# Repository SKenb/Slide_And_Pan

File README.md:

# Slide and Pan

## Overview 

    To give a timelapse that special touch, movement is essential. With this simple self-made and inexpensive slider, one can easily achieve that.

"Slide and Pan" stands for a small, compact, and "all in one" DIY slider.

### All in one

_Just place the Slider and start shooting._

The solution provides one small, solid metal box. (55 x 50 x 145 mm - TODO kg). So all required electronics and mechanics in it and no further motors, batteries, control devices are needed.

### Cheap

_Adjust the expenses to your budget._

One key argument for building an own Slider is the relatively small expenses compared to conventional Sliders. One might also think of requesting prepared or finished parts within a fair price ...

### DIY

_You are the boss_

The plans are no secret and easily be replicated by yourself. Just have a look at the public construction plans or come up with your own modified version.

### App

_Easy control_

Use the built-in rotary encoder or the App, to control the Slider. The App makes it very comfortable to set up movements and plan your shots.

## FEATURES

### Slide

Add linear movement to your Timelapse with the Slide-Feature.
Thereby, the Slider moves along a normed Alu-Profile, and thus any length you can think of is possible...

### Pan

Add some gorgeous rotation to your Timelapse
Keep the Milky Way in the center of the frame or focus another lovely spot during your shooting with the feature of (infinity) rotation of your camera ...

### TRACK

Use the Slider as Star-Tracker and realize detailed DeepSky exposures....

### Control

Select one of the predefined shots with the rotary-encoder or set up a detailed exposure/Timelapse with the inbuilt App...

### Compact

One of the most important factors is to have a small, compact and all in one gadget which fits in every backpack...

### Standalone

Everything included and thus no additional material is needed...

### Powerful

2 x 1500 mAh
Two powerful LiPo-batteries provide Slider with enough energy for several hours of shooting....

### Versatile

Nearly every position and movement one might think of is possible ...

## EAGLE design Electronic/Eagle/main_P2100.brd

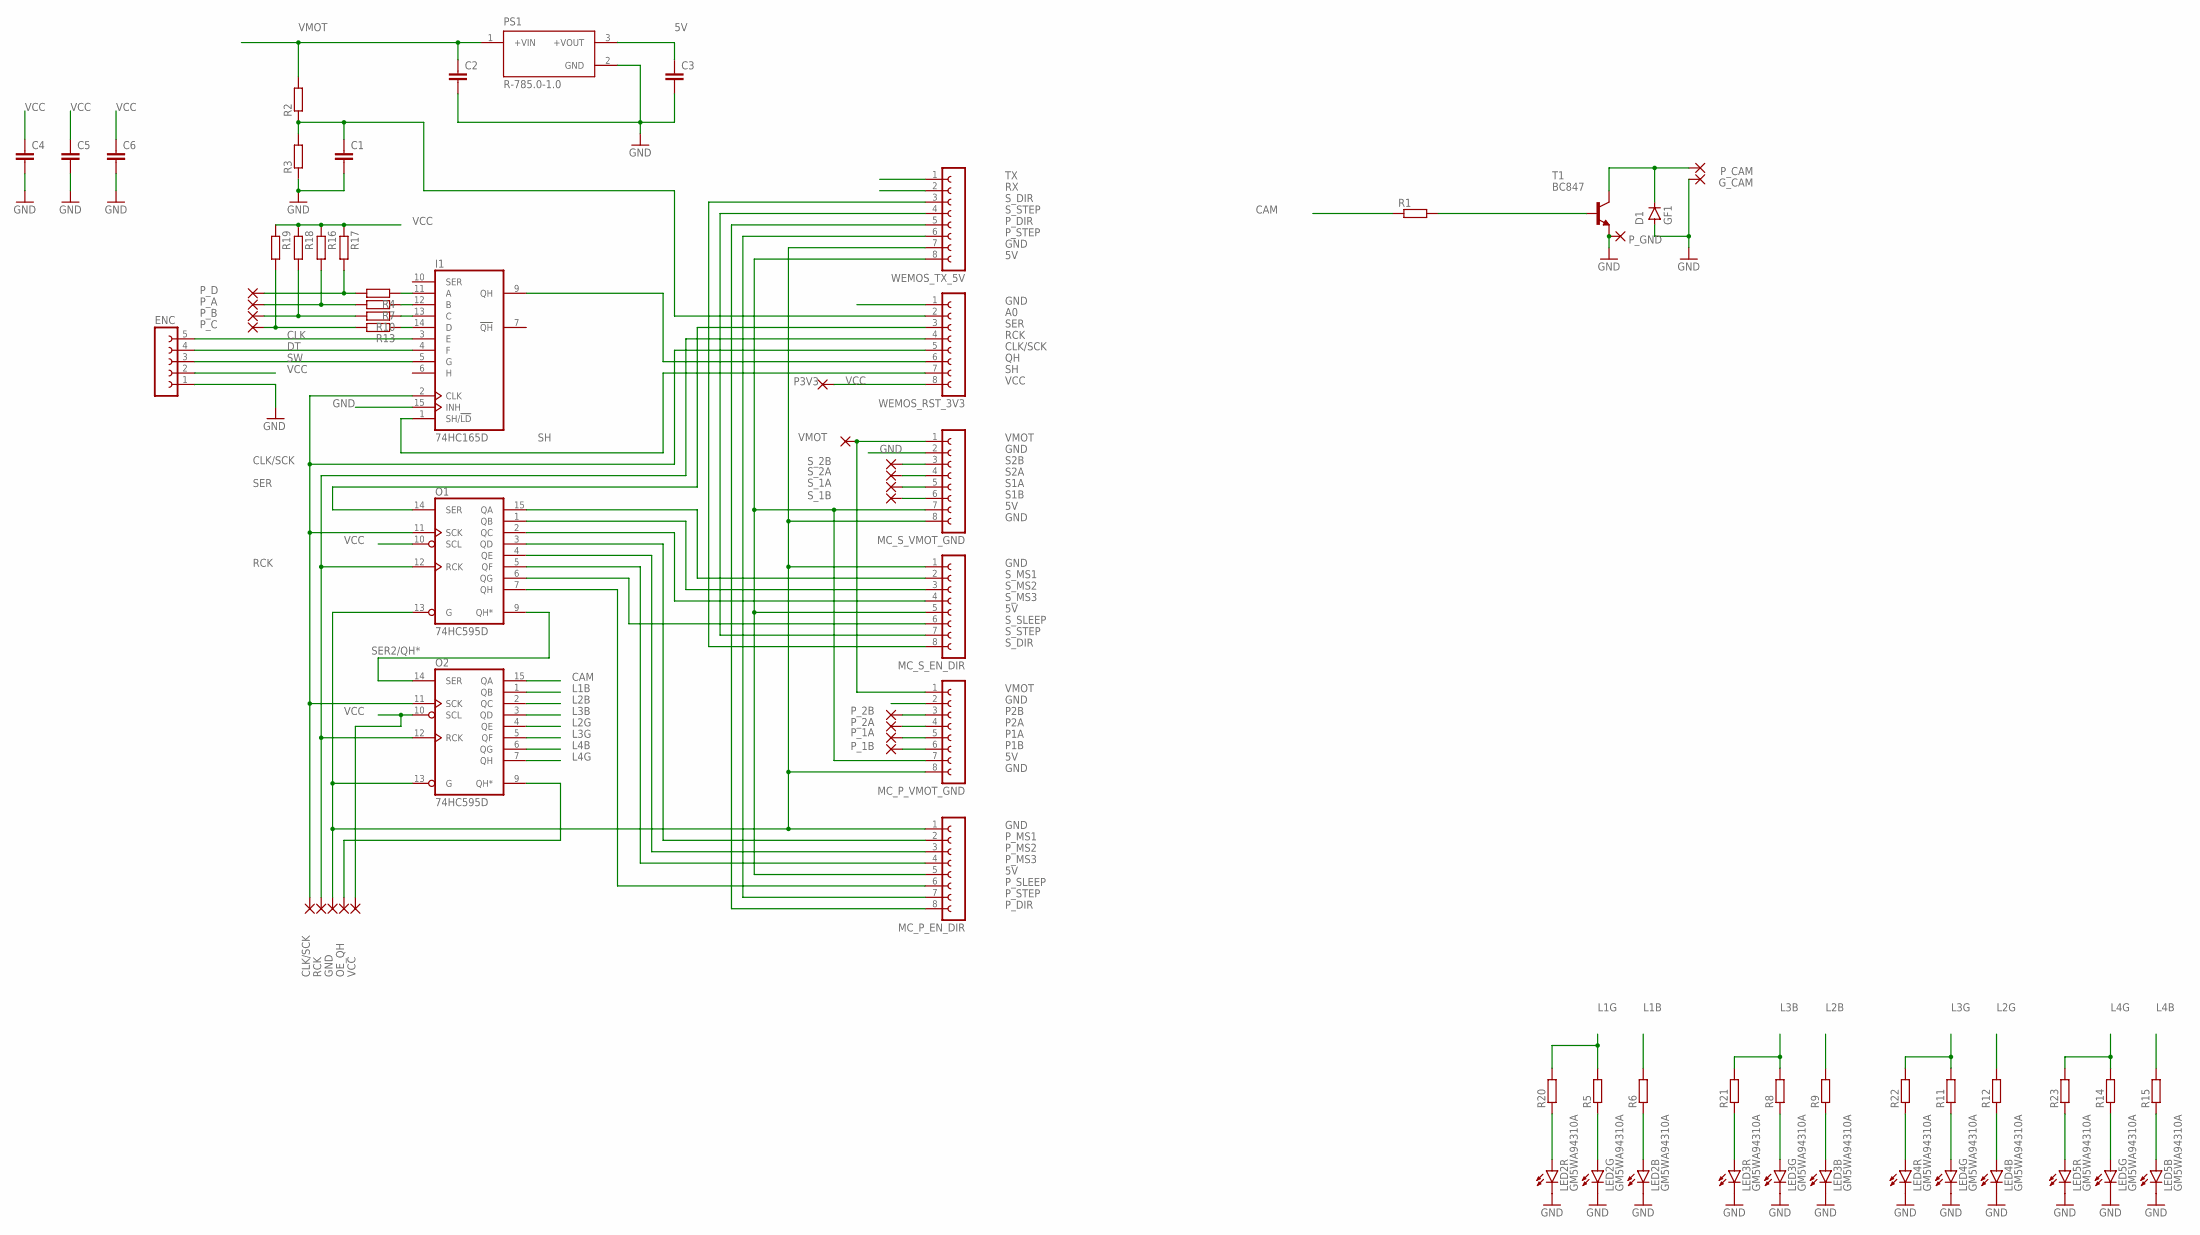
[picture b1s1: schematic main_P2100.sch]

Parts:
C1, C4, C5, C6: C-EUC0603; C0603
C2, C3: C-EUC1206; C1206
D1: GF1; SMA-DO214AC
ENC: FE05-1
G_CAM: SMD5; SMD2,54-5,08
I1: 74HC165D; SO16
LED2, LED3, LED4, LED5: GM5WA94310A
MC_P_EN_DIR: FE08-1; FE08
MC_P_VMOT_GND: FE08-1; FE08
MC_S_EN_DIR: FE08-1; FE08
MC_S_VMOT_GND: FE08-1; FE08
O1, O2: 74HC595D; SO16
P3V3: SMD5; SMD2,54-5,08
PS1: R-785.0-1.0; CONV_R-785.0-1.0
P_1A, P_1B, P_1B1, P_1B2, P_1B3, P_1B4, P_1B5, P_2A, P_2B: SMD5; SMD2,54-5,08
P_A: SMD5; SMD2,54-5,08
P_B: SMD5; SMD2,54-5,08
P_C: SMD5; SMD2,54-5,08
P_CAM: SMD5; SMD2,54-5,08
P_D: SMD5; SMD2,54-5,08
P_GND: SMD5; SMD2,54-5,08
R1, R2, R3, R4, R5, R6, R7, R8, R9, R10, R11, R12, R13, R14, R15, R16, R17, R18, R19, R20, R21, R22, R23: R-EU_R0603; R0603
S_1A, S_1B, S_2A, S_2B: SMD5; SMD2,54-5,08
T1: BC847; SOT23
VMOT: SMD5; SMD2,54-5,08
WEMOS_RST_3V3: FE08-1; FE08
WEMOS_TX_5V: FE08-1; FE08

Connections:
5V: C3.1, MC_P_EN_DIR.5, MC_P_VMOT_GND.7, MC_S_EN_DIR.5, MC_S_VMOT_GND.7, PS1.3 (+VOUT), WEMOS_TX_5V.8
A0: C1.1, R2.1, R3.2, WEMOS_RST_3V3.2
CAM: O2.15 (QA), R1.1
CLK: ENC.5, I1.3 (E)
CLK/SCK: I1.2 (CLK), O1.11 (SCK), O2.11 (SCK), P_1B1.1, WEMOS_RST_3V3.5
DT: ENC.4, I1.4 (F)
GND: C1.2, C2.2, C3.2, C4.2, C5.2, C6.2, D1.A, ENC.1, G_CAM.1, I1.8 (GND), I1.15 (INH), LED2.4 (C), LED2.5 (C), LED2.6 (C), LED3.4 (C), LED3.5 (C), LED3.6 (C), LED4.4 (C), LED4.5 (C), LED4.6 (C), LED5.4 (C), LED5.5 (C), LED5.6 (C), MC_P_EN_DIR.1, MC_P_VMOT_GND.2, MC_P_VMOT_GND.8, MC_S_EN_DIR.1, MC_S_VMOT_GND.2, MC_S_VMOT_GND.8, O1.8 (GND), O1.13 (G), O2.8 (GND), O2.13 (G), PS1.2 (GND), P_1B3.1, P_GND.1, R3.1, T1.2 (E), WEMOS_RST_3V3.1, WEMOS_TX_5V.7
L1B: O2.1 (QB), R6.2
L1G: R5.2, R20.2
L2B: O2.2 (QC), R9.2
L2G: O2.4 (QE), R12.2
L3B: O2.3 (QD), R8.2, R21.2
L3G: O2.5 (QF), R11.2, R22.2
L4B: O2.6 (QG), R15.2
L4G: O2.7 (QH), R14.2, R23.2
unnamed: R1.2, T1.1 (B)
unnamed: D1.K (C), P_CAM.1, T1.3 (C)
unnamed: LED2.3 (A), R5.1
unnamed: LED2.1 (A), R6.1
unnamed: P_D.1, R4.2, R17.2
unnamed: LED3.3 (A), R8.1
unnamed: LED3.1 (A), R9.1
unnamed: P_A.1, R7.2, R16.2
unnamed: LED4.3 (A), R11.1
unnamed: LED4.1 (A), R12.1
unnamed: P_B.1, R10.2, R18.2
unnamed: LED5.3 (A), R14.1
unnamed: LED5.1 (A), R15.1
unnamed: P_C.1, R13.2, R19.2
unnamed: LED2.2 (A), R20.1
unnamed: I1.14 (D), R13.1
unnamed: I1.13 (C), R10.1
unnamed: I1.12 (B), R7.1
unnamed: I1.11 (A), R4.1
unnamed: LED3.2 (A), R21.1
unnamed: LED4.2 (A), R22.1
unnamed: LED5.2 (A), R23.1
OE_QH: O2.9 (QH*), P_1B4.1
P1A: MC_P_VMOT_GND.5, P_1A.1
P1B: MC_P_VMOT_GND.6, P_1B.1
P2A: MC_P_VMOT_GND.4, P_2A.1
P2B: MC_P_VMOT_GND.3, P_2B.1
P_DIR: MC_P_EN_DIR.8, WEMOS_TX_5V.5
P_MS1: MC_P_EN_DIR.2, O1.3 (QD)
P_MS2: MC_P_EN_DIR.3, O1.4 (QE)
P_MS3: MC_P_EN_DIR.4, O1.5 (QF)
P_SLEEP: MC_P_EN_DIR.6, O1.7 (QH)
P_STEP: MC_P_EN_DIR.7, WEMOS_TX_5V.6
QH: I1.9 (QH), WEMOS_RST_3V3.6
RCK: O1.12 (RCK), O2.12 (RCK), P_1B2.1, WEMOS_RST_3V3.4
RX: WEMOS_TX_5V.2
S1A: MC_S_VMOT_GND.5, S_1A.1
S1B: MC_S_VMOT_GND.6, S_1B.1
S2A: MC_S_VMOT_GND.4, S_2A.1
S2B: MC_S_VMOT_GND.3, S_2B.1
SER: O1.14 (SER), WEMOS_RST_3V3.3
SER2/QH*: O1.9 (QH*), O2.14 (SER)
SH: I1.1 (SH/!LD), WEMOS_RST_3V3.7
SW: ENC.3, I1.5 (G)
S_DIR: MC_S_EN_DIR.8, WEMOS_TX_5V.3
S_MS1: MC_S_EN_DIR.2, O1.15 (QA)
S_MS2: MC_S_EN_DIR.3, O1.1 (QB)
S_MS3: MC_S_EN_DIR.4, O1.2 (QC)
S_SLEEP: MC_S_EN_DIR.6, O1.6 (QG)
S_STEP: MC_S_EN_DIR.7, WEMOS_TX_5V.4
TX: WEMOS_TX_5V.1
VCC: C4.1, C5.1, C6.1, ENC.2, I1.16 (VCC), O1.10 (SCL), O1.16 (VCC), O2.10 (SCL), O2.16 (VCC), P3V3.1, P_1B5.1, R16.1, R17.1, R18.1, R19.1, WEMOS_RST_3V3.8
VMOT: C2.1, MC_P_VMOT_GND.1, MC_S_VMOT_GND.1, PS1.1 (+VIN), R2.2, VMOT.1

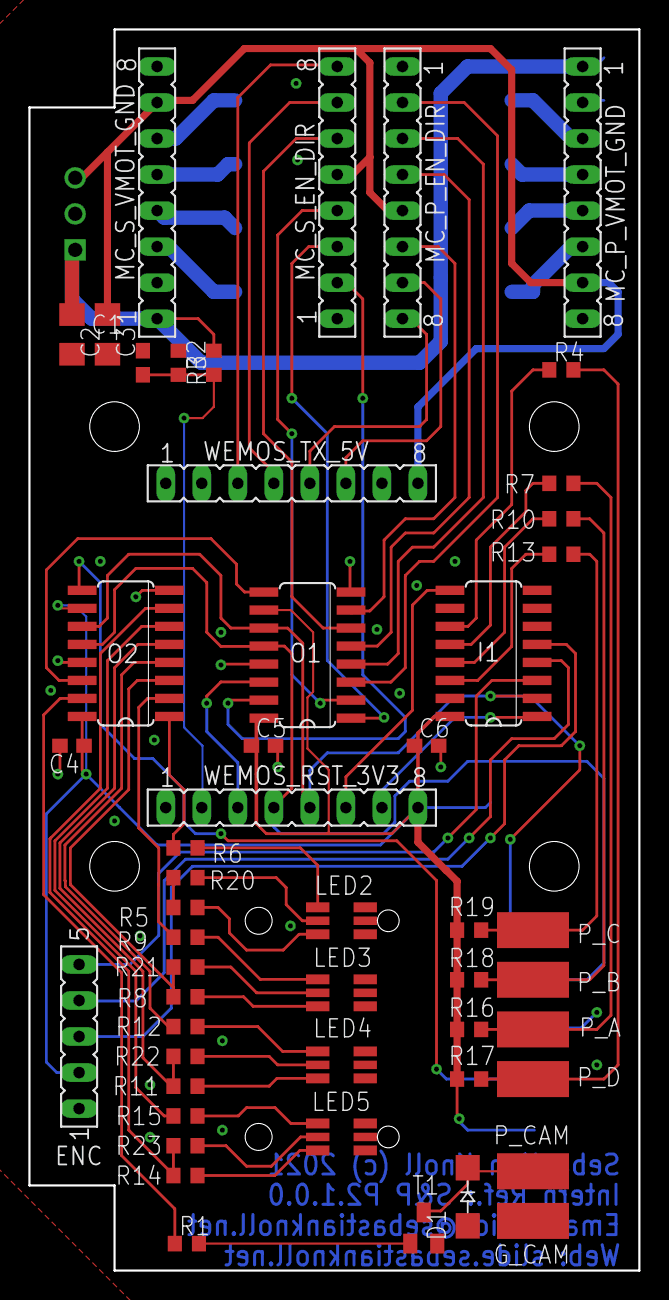
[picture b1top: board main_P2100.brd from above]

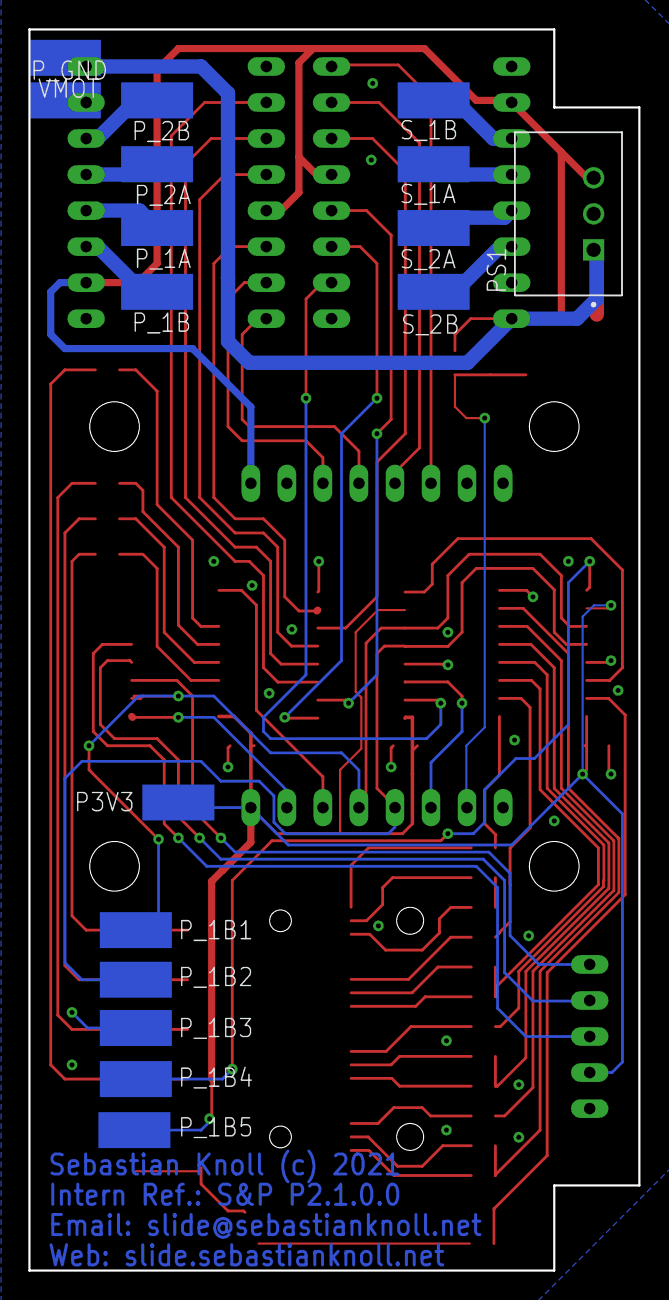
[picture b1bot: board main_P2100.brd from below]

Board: 2 copper layers, 43.0 x 87.5 mm, 68 parts (17 on the bottom side), 66 nets.

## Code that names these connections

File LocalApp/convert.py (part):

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                "%SAP_ID%": "\" + String(SLIDEANDPAN_ID) + \"",
                "%SLIDEANDPAN_ID_INFO%": "\" + String(SLIDEANDPAN_ID_INFO) + \"",
                "%HANDBOOK%": "\" + String(SLIDEANDPAN_LINK_HANDBOOK) + \"",
                "%S_SLEEP%": "\" + String(getSlideStepper()->isSleeping() ? \"Sleeping\" : \"Awake\") + \"",
                "%S_NSLEEP%": "\" + String(getSlideStepper()->isSleeping() ? \"Awake\" : \"Sleep\") + \"",
                "%S_INSLEEP%": "\" + String(getSlideStepper()->isSleeping() ? 1 : 0) + \"",
                "%S_STEPS%": "\" + String(getSlideStepper()->getSteps()) + \"",
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                "%S_PHY_VALUE_DES%": "\" + (getSlideStepper()->getPhysicalValueDescription()) + \"",
                "%S_PHY_VALUE%": "\" + (getSlideStepper()->getPhysicalValueInfo()) + \"",
                "%S_PHY_VALUE_UNIT%": "\" + (getSlideStepper()->getPhysicalValueUnit()) + \"",
                "%S_DIR_PIN%": "\" + String(SLIDE_STEPPER_PIN_DIRECTION) + \"",
                "%S_STEP_PIN%": "\" + String(SLIDE_STEPPER_PIN_STEP) + \"",
                "%S_SLEEP_PIN%": "\" + String(SLIDE_STEPPER_PIN_SLEEP) + \"",
                "%S_STEPS_PER_TURN%": "\" + String(STEPPER_STEPS_PER_TURN) + \"",
                "%S_CAN_CHANGE_RES%": "\" + String(getSlideStepper()->hasChangeResolutionMethod() ? \"Yes\" : \"No\") + \"",
                "%S_DRIVER_M1%": "\" + String(SLIDE_STEPPER_DRIVER_M1) + \"",
                "%S_DRIVER_M2%": "\" + String(SLIDE_STEPPER_DRIVER_M2) + \"",
                "%S_DRIVER_M3%": "\" + String(SLIDE_STEPPER_DRIVER_M3) + \"",
                "%P_SLEEP%": "\" + String(getPanStepper()->isSleeping() ? \"Sleeping\" : \"Awake\") + \"",
                "%P_NSLEEP%": "\" + String(getPanStepper()->isSleeping() ? \"Awake\" : \"Sleep\") + \"",
                "%P_INSLEEP%": "\" + String(getPanStepper()->isSleeping() ? 1 : 0) + \"",
                "%P_STEPS%": "\" + String(getPanStepper()->getSteps()) + \"",
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                "%P_PHY_VALUE_DES%": "\" + (getPanStepper()->getPhysicalValueDescription()) + \"",
                "%P_PHY_VALUE%": "\" + (getPanStepper()->getPhysicalValueInfo()) + \"",
                "%P_PHY_VALUE_UNIT%": "\" + (getPanStepper()->getPhysicalValueUnit()) + \"",
                "%P_DIR_PIN%": "\" + String(PAN_STEPPER_PIN_DIRECTION) + \"",
                "%P_STEP_PIN%": "\" + String(PAN_STEPPER_PIN_STEP) + \"",
                "%P_SLEEP_PIN%": "\" + String(PAN_STEPPER_PIN_SLEEP) + \"",
                "%P_STEPS_PER_TURN%": "\" + String(STEPPER_STEPS_PER_TURN) + \"",
                "%P_CAN_CHANGE_RES%": "\" + String(getPanStepper()->hasChangeResolutionMethod() ? \"Yes\" : \"No\") + \"",
                "%P_DRIVER_M1%": "\" + String(PAN_STEPPER_DRIVER_M1) + \"",
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
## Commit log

2020-03-29 Repo init
2020-03-29 Timer consts and waitUntilTargetReached
2020-03-30 Accelaration
2020-04-12 IOBoard
2020-04-12 Rotate with encoder
2020-04-30 ChangeResolution + Strucutre update
2020-05-04 Ajas stream
2020-05-14 Basic command via Web possible
2020-09-10 V 1.0.0.7
2021-01-16 Wesite stuff
2021-01-16 Open Beta - Website crash fix and led fix
2021-01-21 local App Init
2021-01-21 App integration
2021-01-28 Local App update
2021-02-02 using F(str) for webiste - appcontrol
2021-03-11 Electronic init commit
2021-03-11 Move Firmware
2021-03-11 Organization init commit
2021-03-11 Construciton init commit
2021-04-08 Brdige
2021-04-08 2 new Images
2021-04-08 Dleete wrong bridge stuff
2021-04-09 Bridge Version 1.0.1
2021-04-09 Bridge Finished Ver. 1
2021-04-14 Some plans - drawio
2022-03-02 Set theme jekyll-theme-architect
2022-03-02 Create CNAME

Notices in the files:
Electronic/Eagle/main_P2100.brd:
Sebastian Knoll (c) 2021
